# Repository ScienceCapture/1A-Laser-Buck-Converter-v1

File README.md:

# 1A-Laser-Buck-Converter-v1

This miniature laser diode driver is capable delivering up to 1A of constant current. With its small size of only 15x10 mm (0.6x0.4 inches) it’s suitable for projects with limited enclosure space. The constant current value is fixed. It can be changed by swapping out the 1206 sized resistor (the value is given in the PAM2804 datasheet)

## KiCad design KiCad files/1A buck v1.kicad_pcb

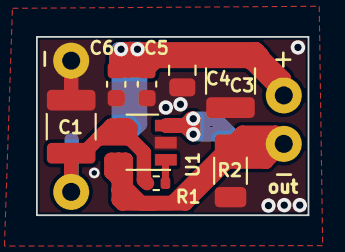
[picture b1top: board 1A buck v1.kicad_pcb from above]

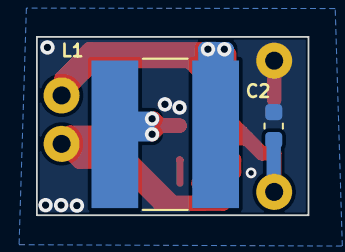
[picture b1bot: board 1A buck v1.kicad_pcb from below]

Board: 2 copper layers, 15.1 x 9.9 mm, 14 parts (2 on the bottom side), 6 nets.

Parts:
+: MountingHole_Pad; MountingHole_2.5mm_Pad
-: MountingHole_Pad; MountingHole_2.5mm_Pad
-#2: MountingHole_Pad; MountingHole_2.5mm_Pad
C1: 10uF; C_1210_3225Metric
C2: 10uF; C_0603_1608Metric
C3: 47uF; C_1210_3225Metric
C4: 10uF; C_0805_2012Metric
C5: 1uF; C_0603_1608Metric
C6: 100nF; C_0603_1608Metric
H2: MountingHole_Pad; MountingHole_2mm_Pad_Giannis_custom
L1: 4.7uH; L_Bourns-SRN8040_8x8.15mm
R1: 10k; R_0402_1005Metric
R2: 0.33R; R_1206_3216Metric
U1: PAM2804; TSOT-23-5

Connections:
GND: C1.2, C2.2, C3.2, C4.2, C5.2, C6.2, H2.1, R2.2, U1.2
unnamed: L1.1, U1.3
unnamed: R1.1, U1.1
OUT+: +.1, C3.1, C4.1, C5.1, C6.1, L1.2
OUT-: -.1, R2.1, U1.5
VCC: -#2.1, C1.1, C2.1, R1.2, U1.4
